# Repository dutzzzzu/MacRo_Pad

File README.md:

## MacRo Pad

A compact macropad with 6 keys, 2 rotary encoders, and a small OLED display.  
It’s designed for quick media control, productivity shortcuts, and future smart home integration.  
Currently built for macOS. Home Assistant integration and Windows support will be added once the hardware is available.

---
## Overview

<table>
  <tr>
    <td align="center">
      <b>Render</b><br>
      
    </td>
    <td align="center">
      <b>Case</b><br>
      
    </td>
  </tr>
  <tr>
    <td align="center">
      <b>Schematic</b><br>
      
    </td>
    <td align="center">
      <b>PCB</b><br>
      
    </td>
  </tr>
</table>

---

## Bill of Materials

| Part | Quantity | Notes |
|------|--------|------|
| Seeed XIAO RP2040 | 1 | Main microcontroller |
| MX-style switches | 6 | Mechanical switches |
| DSA keycaps | 6 | Keycaps |
| EC11 rotary encoders | 2 | Rotation only |
| 0.91" OLED display (SSD1306) | 1 | I2C |
| 1N4148 diodes | 6 | Key matrix |
| Custom PCB | 1 | Designed in KiCad |
| 3D printed case | 1 | Custom enclosure |
| 3D printed knobs | 2 | Custom knobs |
| M3 screws | 1 | Assembly |
| M3 heatset inserts | 1 | Mounting |

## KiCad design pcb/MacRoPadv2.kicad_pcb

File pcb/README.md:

PCB design files for the macropad.
The assembly is made in fusion
## PCB Design

| Layout | PCB (no buttons) |
|-----------|------------------|
|  |  |

|   Schematic | All Components |
|-----------|---------------|
| |  |

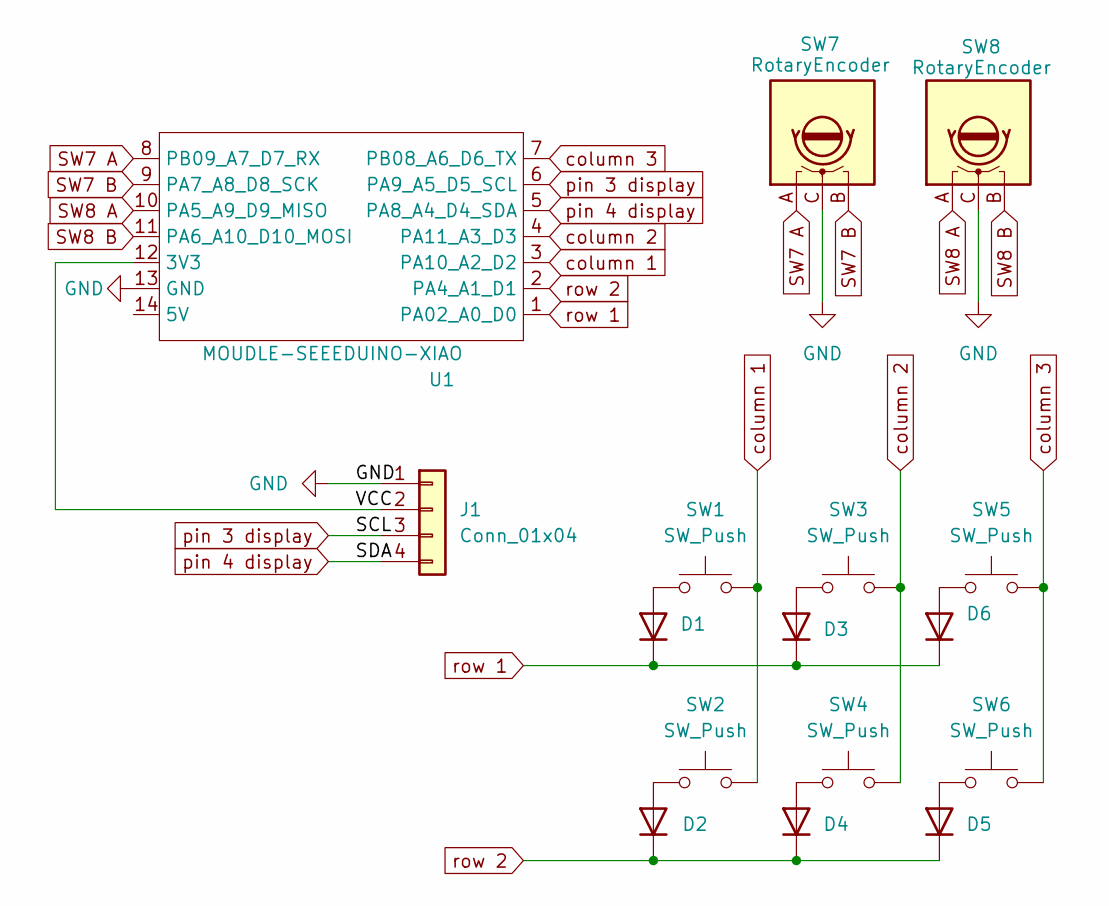
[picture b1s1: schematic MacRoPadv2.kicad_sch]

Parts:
D1, D2, D3, D4, D5, D6: 1N4148; D_DO-35_SOD27_P7.62mm_Horizontal
J1: Conn_01x04; SSD1306-0.91-OLED-4pin-128x32
SW1, SW2, SW3, SW4, SW5, SW6: SW_Push; SW_Cherry_MX_1.00u_PCB
SW7, SW8: RotaryEncoder; RotaryEncoder_Alps_EC11E-Switch_Vertical_H20mm
U1: MOUDLE-SEEEDUINO-XIAO; XIAO-RP2040-DIP

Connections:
/VCC: J1.2, U1.12 (3V3)
GND: J1.1, SW7.C, SW8.C, U1.13 (GND)
unnamed: D1.2 (A), SW1.1
unnamed: D2.2 (A), SW2.1
unnamed: D3.2 (A), SW3.1
unnamed: D4.2 (A), SW4.1
unnamed: D5.2 (A), SW6.1
unnamed: D6.2 (A), SW5.1
SW7 A: SW7.A, U1.8 (PB09_A7_D7_RX)
SW7 B: SW7.B, U1.9 (PA7_A8_D8_SCK)
SW8 A: SW8.A, U1.10 (PA5_A9_D9_MISO)
SW8 B: SW8.B, U1.11 (PA6_A10_D10_MOSI)
column 1: SW1.2, SW2.2, U1.3 (PA10_A2_D2)
column 2: SW3.2, SW4.2, U1.4 (PA11_A3_D3)
column 3: SW5.2, SW6.2, U1.7 (PB08_A6_D6_TX)
pin 3 display: J1.3, U1.6 (PA9_A5_D5_SCL)
pin 4 display: J1.4, U1.5 (PA8_A4_D4_SDA)
row 1: D1.1 (K), D3.1 (K), D6.1 (K), U1.1 (PA02_A0_D0)
row 2: D2.1 (K), D4.1 (K), D5.1 (K), U1.2 (PA4_A1_D1)

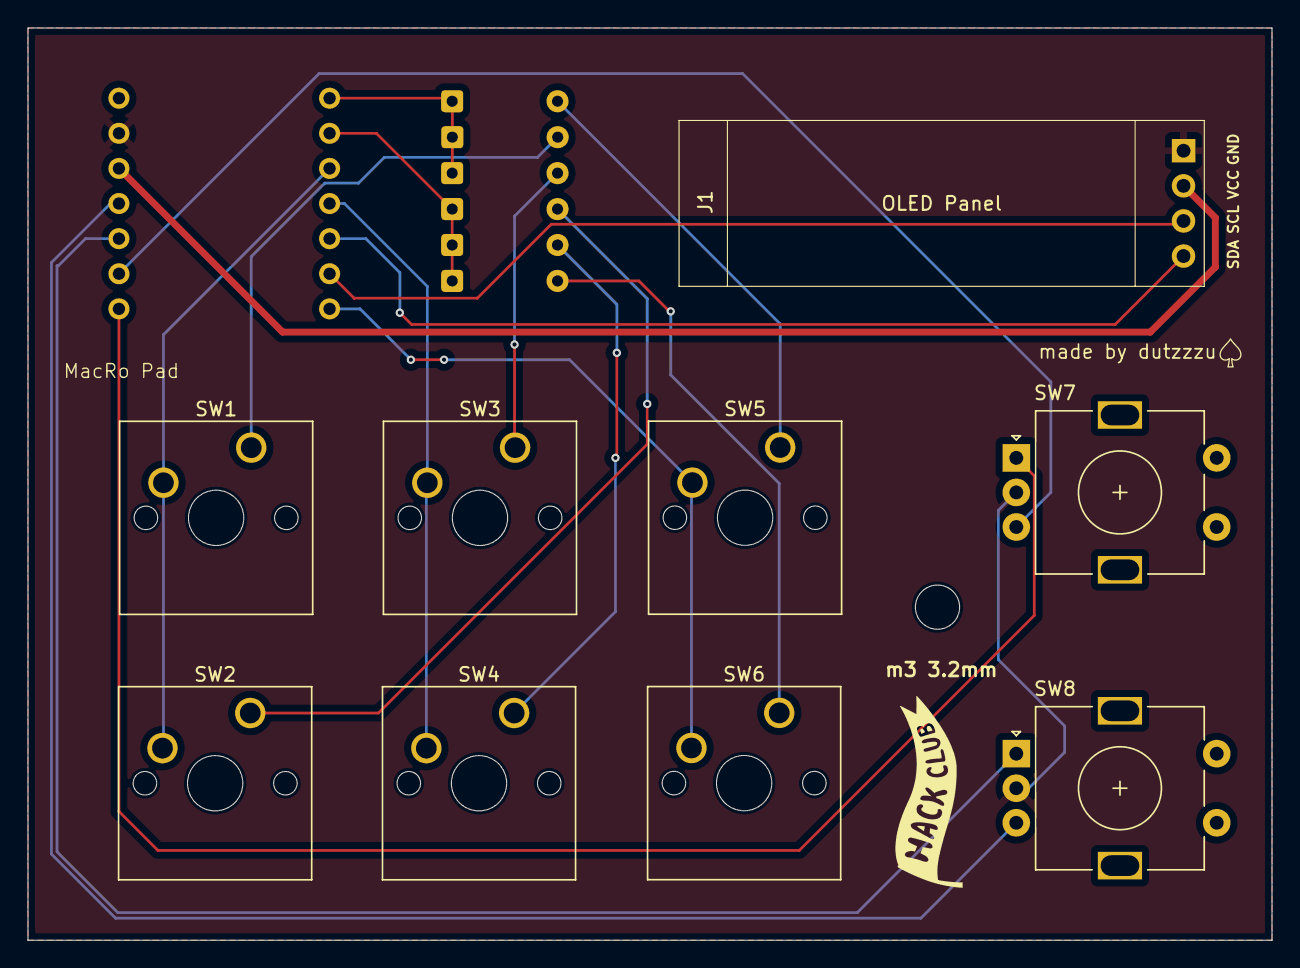
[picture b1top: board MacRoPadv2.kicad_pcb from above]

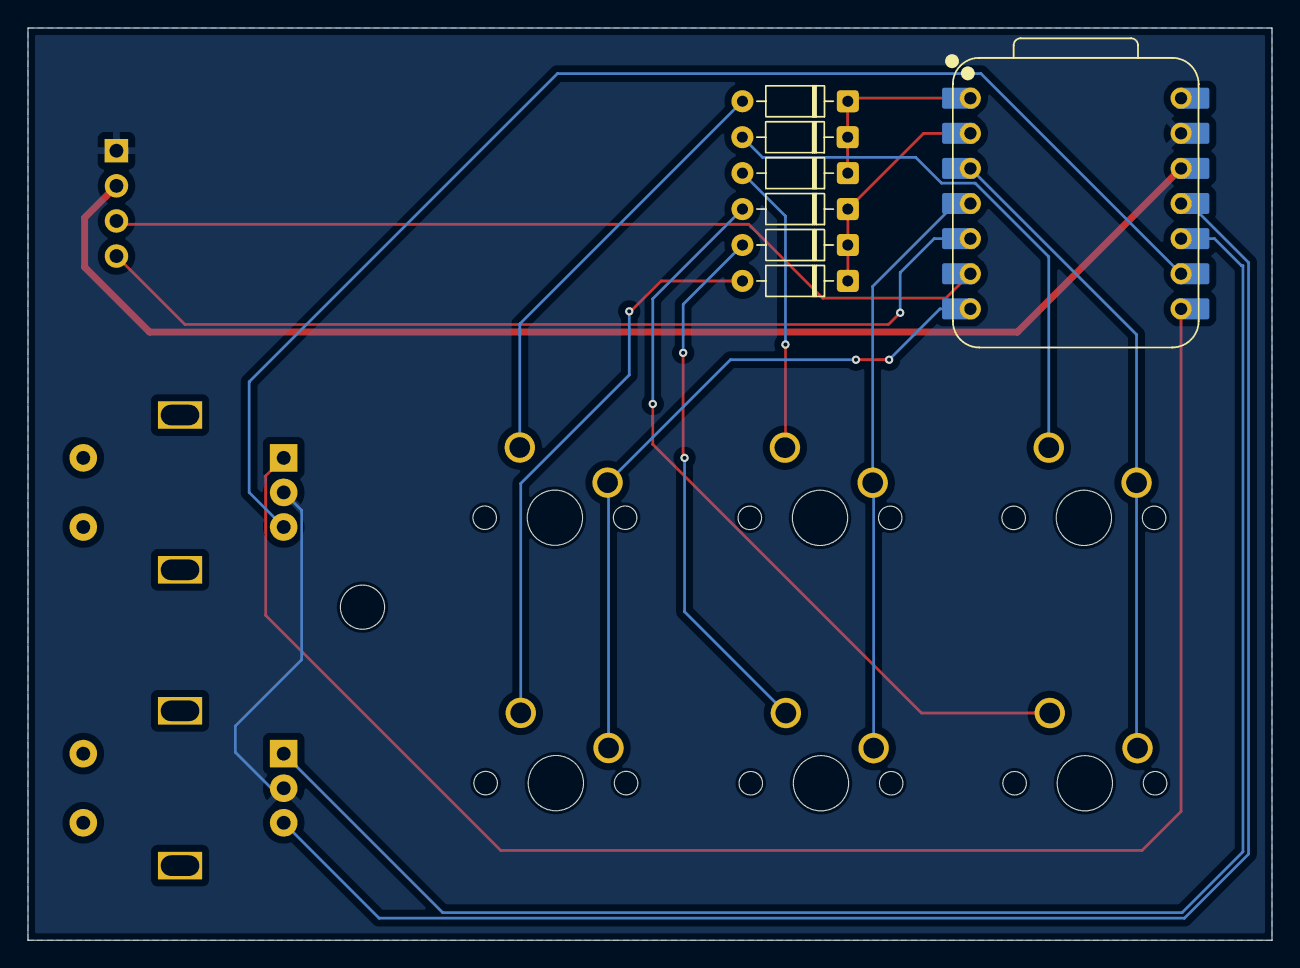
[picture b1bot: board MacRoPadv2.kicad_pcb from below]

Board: 2 copper layers, 90.0 x 66.0 mm, 16 parts (7 on the bottom side), 19 nets.

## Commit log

2026-03-08 photos
2026-03-08 Create photos
